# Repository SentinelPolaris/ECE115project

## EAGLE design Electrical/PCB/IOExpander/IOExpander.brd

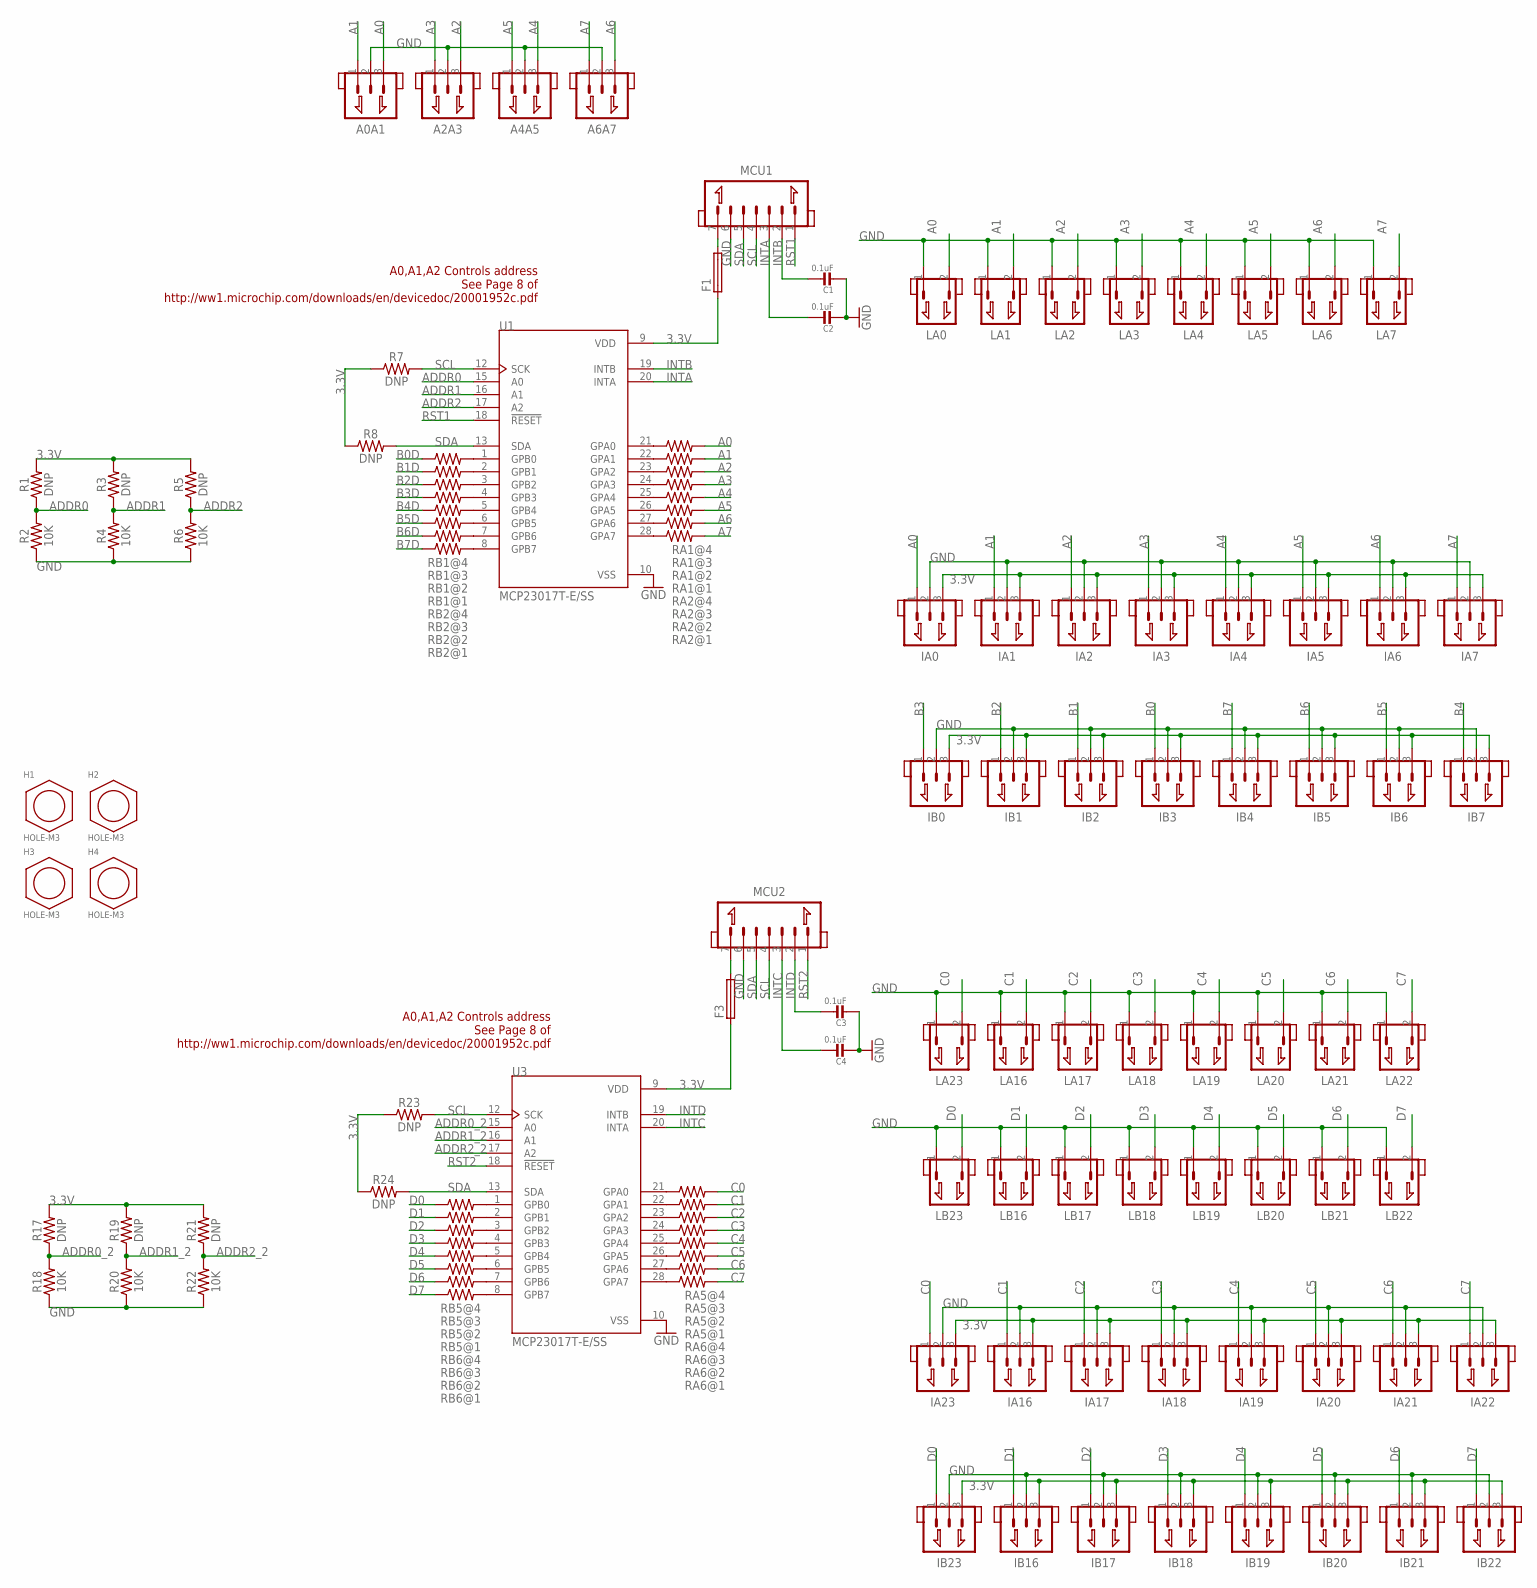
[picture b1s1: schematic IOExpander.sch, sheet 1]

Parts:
A0A1, A2A3, A4A5, A6A7: JST_1.25_3P; JST1.25_3P
C1, C2, C3, C4: 0.1uF; 0603
F1, F3: FUSE-0603; 0603
H1, H2, H3, H4: HOLE-M3; M3
IA0, IA1, IA2, IA3, IA4, IA5, IA6, IA7, IA16, IA17, IA18, IA19, IA20, IA21, IA22, IA23: JST_1.25_3P; JST1.25_3P
IB0, IB1, IB2, IB3, IB4, IB5, IB6, IB7, IB16, IB17, IB18, IB19, IB20, IB21, IB22, IB23: JST_1.25_3P; JST1.25_3P
LA0, LA1, LA2, LA3, LA4, LA5, LA6, LA7, LA16, LA17, LA18, LA19, LA20, LA21, LA22, LA23: JST_1.25_2P; JST1.25_2P
LB16, LB17, LB18, LB19, LB20, LB21, LB22, LB23: JST_1.25_2P; JST1.25_2P
MCU1, MCU2: JST_1.25_7P; JST1.25_7P
R1, R3, R5, R7, R8, R17, R19, R21, R23, R24: DNP; 0603
R2, R4, R6, R18, R20, R22: 10K; 0603
RA1, RA2, RA5, RA6: RESISTOR_ARRAY_1206_SEPARATE; RESCAF80P320X160X60-8N
RB1, RB2, RB5, RB6: RESISTOR_ARRAY_1206_SEPARATE_REVERSE; RESCAF80P320X160X60-8N
U1, U3: MCP23017T-E/SS; SOP65P780X200-28N

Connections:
3.3V: F1.1, F3.1, IA0.3, IA1.3, IA2.3, IA3.3, IA4.3, IA5.3, IA6.3, IA7.3, IA16.3, IA17.3, IA18.3, IA19.3, IA20.3, IA21.3, IA22.3, IA23.3, IB0.3, IB1.3, IB2.3, IB3.3, IB4.3, IB5.3, IB6.3, IB7.3, IB16.3, IB17.3, IB18.3, IB19.3, IB20.3, IB21.3, IB22.3, IB23.3, R1.2, R3.2, R5.2, R7.1, R8.1, R17.2, R19.2, R21.2, R23.1, R24.1, U1.9 (VDD), U3.9 (VDD); also elsewhere on the board
A0: A0A1.3, IA0.1, LA0.2, RA1.5 (2)
A1: A0A1.1, IA1.1, LA1.2, RA1.6 (2)
A2: A2A3.3, IA2.1, LA2.2, RA1.7 (2)
A3: A2A3.1, IA3.1, LA3.2, RA1.8 (2)
A4: A4A5.3, IA4.1, LA4.2, RA2.5 (2)
A5: A4A5.1, IA5.1, LA5.2, RA2.6 (2)
A6: A6A7.3, IA6.1, LA6.2, RA2.7 (2)
A7: A6A7.1, IA7.1, LA7.2, RA2.8 (2)
ADDR0: R1.1, R2.2, U1.15 (A0)
ADDR0_2: R17.1, R18.2, U3.15 (A0)
ADDR1: R3.1, R4.2, U1.16 (A1)
ADDR1_2: R19.1, R20.2, U3.16 (A1)
ADDR2: R5.1, R6.2, U1.17 (A2)
ADDR2_2: R21.1, R22.2, U3.17 (A2)
B0: IB3.1; also elsewhere on the board
B0D: RB1.5 (1); also elsewhere on the board
B1: IB2.1; also elsewhere on the board
B1D: RB1.6 (1); also elsewhere on the board
B2: IB1.1; also elsewhere on the board
B2D: RB1.7 (1); also elsewhere on the board
B3: IB0.1; also elsewhere on the board
B3D: RB1.8 (1); also elsewhere on the board
B4: IB7.1; also elsewhere on the board
B4D: RB2.5 (1); also elsewhere on the board
B5: IB6.1; also elsewhere on the board
B5D: RB2.6 (1); also elsewhere on the board
B6: IB5.1; also elsewhere on the board
B6D: RB2.7 (1); also elsewhere on the board
B7: IB4.1; also elsewhere on the board
B7D: RB2.8 (1); also elsewhere on the board
C0: IA23.1, LA23.2, RA5.5 (2)
C1: IA16.1, LA16.2, RA5.6 (2)
C2: IA17.1, LA17.2, RA5.7 (2)
C3: IA18.1, LA18.2, RA5.8 (2)
C4: IA19.1, LA19.2, RA6.5 (2)
C5: IA20.1, LA20.2, RA6.6 (2)
C6: IA21.1, LA21.2, RA6.7 (2)
C7: IA22.1, LA22.2, RA6.8 (2)
D0: IB23.1, LB23.2, RB5.5 (1)
D1: IB16.1, LB16.2, RB5.6 (1)
D2: IB17.1, LB17.2, RB5.7 (1)
D3: IB18.1, LB18.2, RB5.8 (1)
D4: IB19.1, LB19.2, RB6.5 (1)
D5: IB20.1, LB20.2, RB6.6 (1)
D6: IB21.1, LB21.2, RB6.7 (1)
D7: IB22.1, LB22.2, RB6.8 (1)
GND: A0A1.2, A2A3.2, A4A5.2, A6A7.2, C1.2, C2.2, C3.2, C4.2, IA0.2, IA1.2, IA2.2, IA3.2, IA4.2, IA5.2, IA6.2, IA7.2, IA16.2, IA17.2, IA18.2, IA19.2, IA20.2, IA21.2, IA22.2, IA23.2, IB0.2, IB1.2, IB2.2, IB3.2, IB4.2, IB5.2, IB6.2, IB7.2, IB16.2, IB17.2, IB18.2, IB19.2, IB20.2, IB21.2, IB22.2, IB23.2, LA0.1, LA1.1, LA2.1, LA3.1, LA4.1, LA5.1, LA6.1, LA7.1, LA16.1, LA17.1, LA18.1, LA19.1, LA20.1, LA21.1, LA22.1, LA23.1, LB16.1, LB17.1, LB18.1, LB19.1, LB20.1, LB21.1, LB22.1, LB23.1, MCU1.6, MCU2.6, R2.1, R4.1, R6.1, R18.1, R20.1, R22.1, U1.10 (VSS), U3.10 (VSS); also elsewhere on the board
INTA: C2.1, MCU1.3, U1.20 (INTA)
INTB: C1.1, MCU1.2, U1.19 (INTB)
INTC: C4.1, MCU2.3, U3.20 (INTA)
INTD: C3.1, MCU2.2, U3.19 (INTB)
unnamed: RA1.1, U1.24 (GPA3)
unnamed: RA1.2 (1), U1.23 (GPA2)
unnamed: RA1.3 (1), U1.22 (GPA1)
unnamed: RA1.4 (1), U1.21 (GPA0)
unnamed: RA2.1, U1.28 (GPA7)
unnamed: RA2.2 (1), U1.27 (GPA6)
unnamed: RA2.3 (1), U1.26 (GPA5)
unnamed: RA2.4 (1), U1.25 (GPA4)
unnamed: F1.2, MCU1.7
unnamed: RB1.1 (2), U1.4 (GPB3)
unnamed: RB1.2, U1.3 (GPB2)
unnamed: RB1.3 (2), U1.2 (GPB1)
unnamed: RB1.4 (2), U1.1 (GPB0)
unnamed: RB2.1 (2), U1.8 (GPB7)
unnamed: RB2.2, U1.7 (GPB6)
unnamed: RB2.3 (2), U1.6 (GPB5)
unnamed: RB2.4 (2), U1.5 (GPB4)
unnamed: F3.2, MCU2.7
unnamed: RB5.1 (2), U3.4 (GPB3)
unnamed: RB5.2, U3.3 (GPB2)
unnamed: RB5.3 (2), U3.2 (GPB1)
unnamed: RB5.4 (2), U3.1 (GPB0)
unnamed: RB6.1 (2), U3.8 (GPB7)
unnamed: RB6.2, U3.7 (GPB6)
unnamed: RB6.3 (2), U3.6 (GPB5)
unnamed: RB6.4 (2), U3.5 (GPB4)
unnamed: RA5.1, U3.24 (GPA3)
unnamed: RA5.2 (1), U3.23 (GPA2)
unnamed: RA5.3 (1), U3.22 (GPA1)
unnamed: RA5.4 (1), U3.21 (GPA0)
unnamed: RA6.1, U3.28 (GPA7)
unnamed: RA6.2 (1), U3.27 (GPA6)
unnamed: RA6.3 (1), U3.26 (GPA5)
unnamed: RA6.4 (1), U3.25 (GPA4)
RST1: MCU1.1, U1.18 (!RESET)
RST2: MCU2.1, U3.18 (!RESET)
SCL: MCU1.4, MCU2.4, R7.2, R23.2, U1.12 (SCK), U3.12 (SCK)
SDA: MCU1.5, MCU2.5, R8.2, R24.2, U1.13 (SDA), U3.13 (SDA)

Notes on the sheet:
A0,A1,A2 Controls address See Page 8 of http://ww1.microchip.com/downloads/en/devicedoc/20001952c.pdf

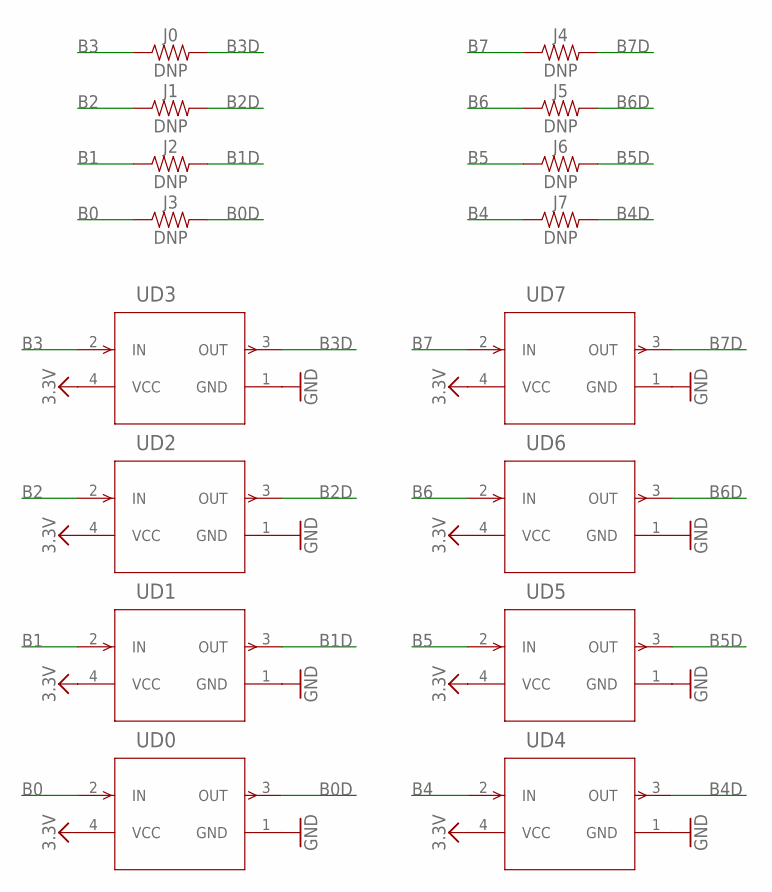
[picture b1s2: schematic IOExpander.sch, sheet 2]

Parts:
J0, J1, J2, J3, J4, J5, J6, J7: DNP; 0603
UD0, UD1, UD2, UD3, UD4, UD5, UD6, UD7: DEBOUNCE_MAX6816EUS+T; 21-0052F

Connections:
3.3V: UD0.4 (VCC), UD1.4 (VCC), UD2.4 (VCC), UD3.4 (VCC), UD4.4 (VCC), UD5.4 (VCC), UD6.4 (VCC), UD7.4 (VCC); also elsewhere on the board
B0: J3.1, UD0.2 (IN); also elsewhere on the board
B0D: J3.2, UD0.3 (OUT); also elsewhere on the board
B1: J2.1, UD1.2 (IN); also elsewhere on the board
B1D: J2.2, UD1.3 (OUT); also elsewhere on the board
B2: J1.1, UD2.2 (IN); also elsewhere on the board
B2D: J1.2, UD2.3 (OUT); also elsewhere on the board
B3: J0.1, UD3.2 (IN); also elsewhere on the board
B3D: J0.2, UD3.3 (OUT); also elsewhere on the board
B4: J7.1, UD4.2 (IN); also elsewhere on the board
B4D: J7.2, UD4.3 (OUT); also elsewhere on the board
B5: J6.1, UD5.2 (IN); also elsewhere on the board
B5D: J6.2, UD5.3 (OUT); also elsewhere on the board
B6: J5.1, UD6.2 (IN); also elsewhere on the board
B6D: J5.2, UD6.3 (OUT); also elsewhere on the board
B7: J4.1, UD7.2 (IN); also elsewhere on the board
B7D: J4.2, UD7.3 (OUT); also elsewhere on the board
GND: UD0.1 (GND), UD1.1 (GND), UD2.1 (GND), UD3.1 (GND), UD4.1 (GND), UD5.1 (GND), UD6.1 (GND), UD7.1 (GND); also elsewhere on the board

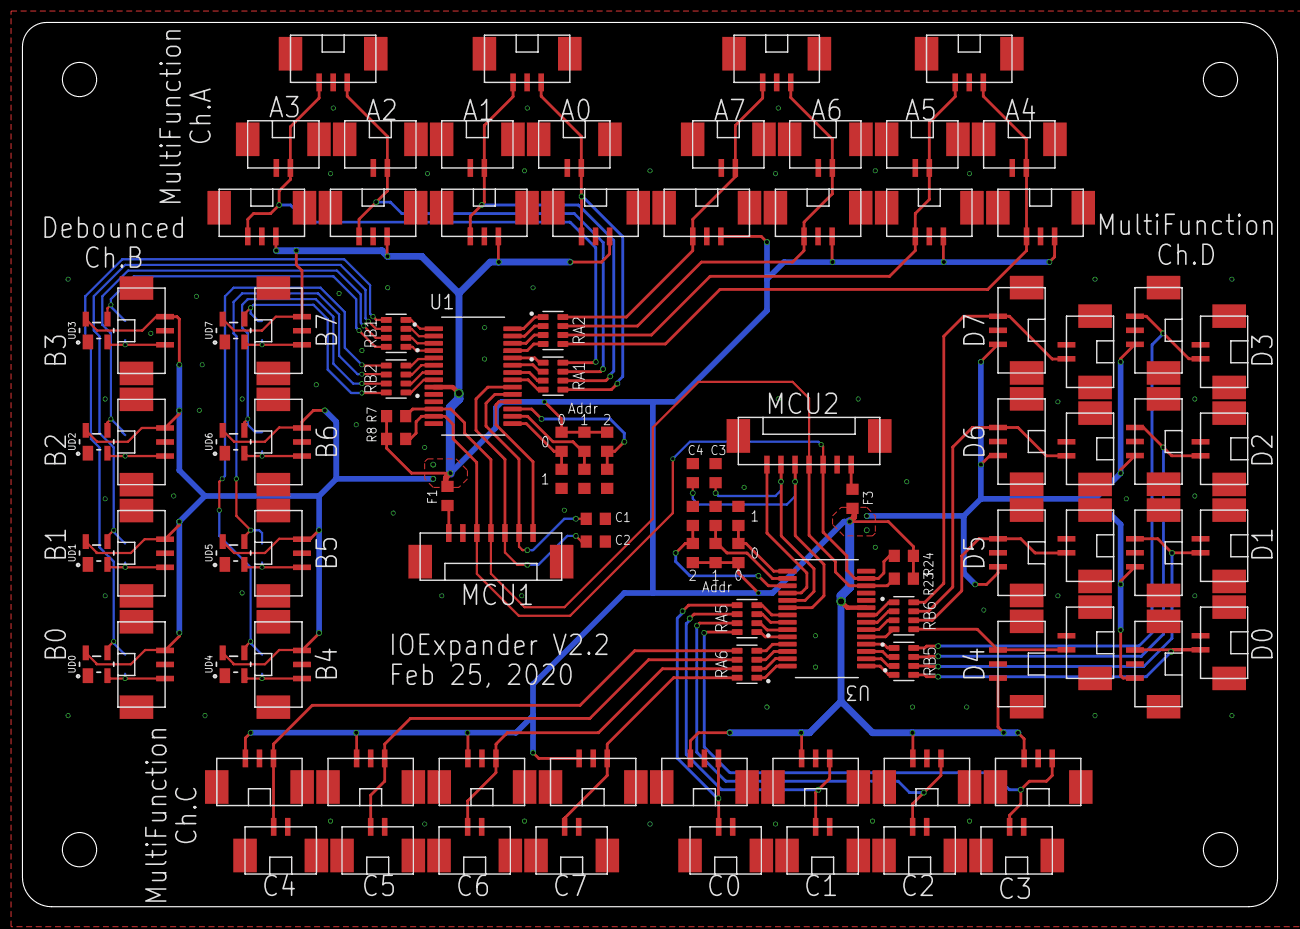
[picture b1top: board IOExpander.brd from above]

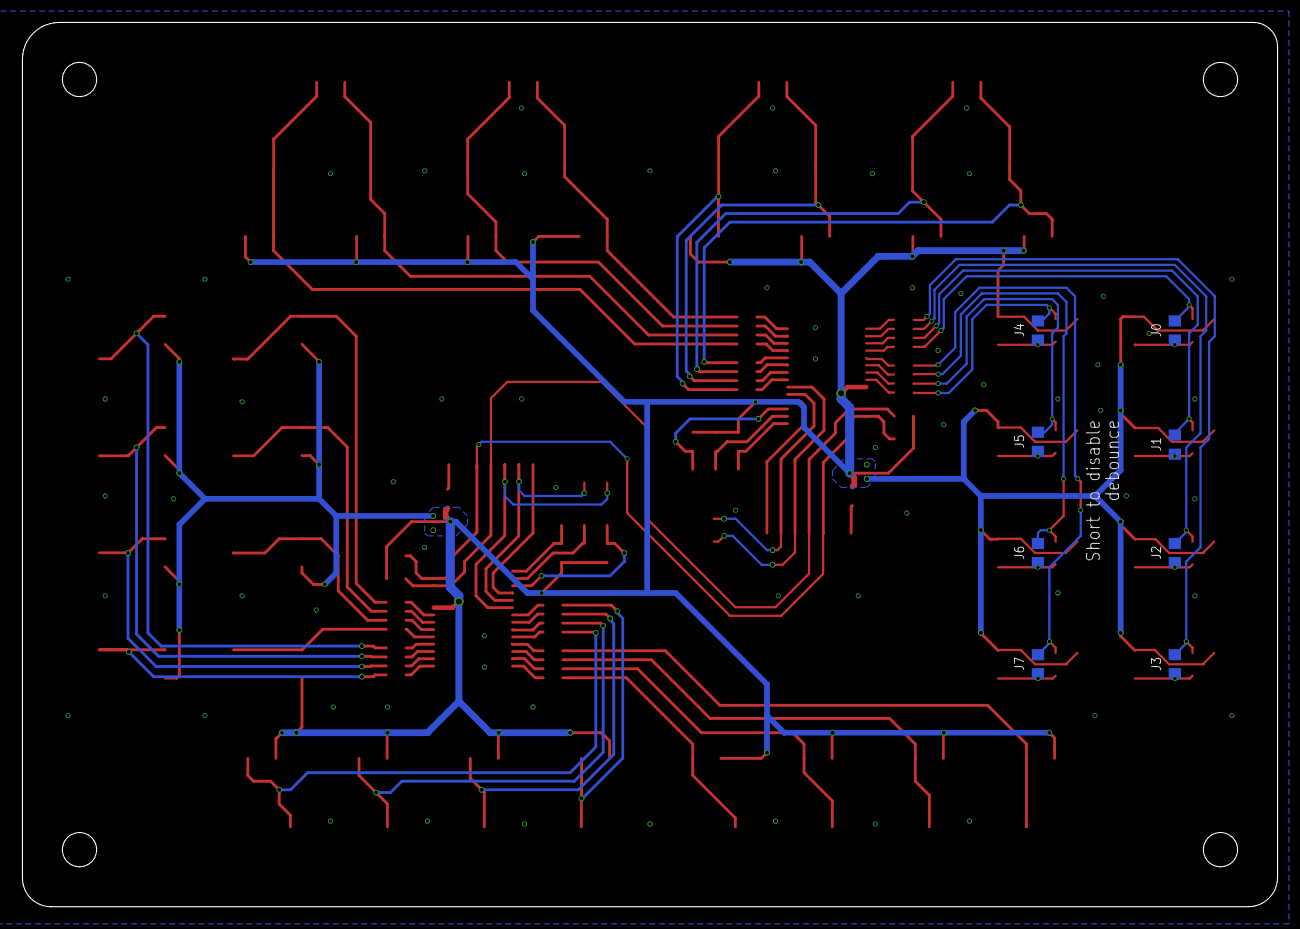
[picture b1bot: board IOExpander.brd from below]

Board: 2 copper layers, 111.8 x 78.7 mm, 114 parts (8 on the bottom side), 90 nets.

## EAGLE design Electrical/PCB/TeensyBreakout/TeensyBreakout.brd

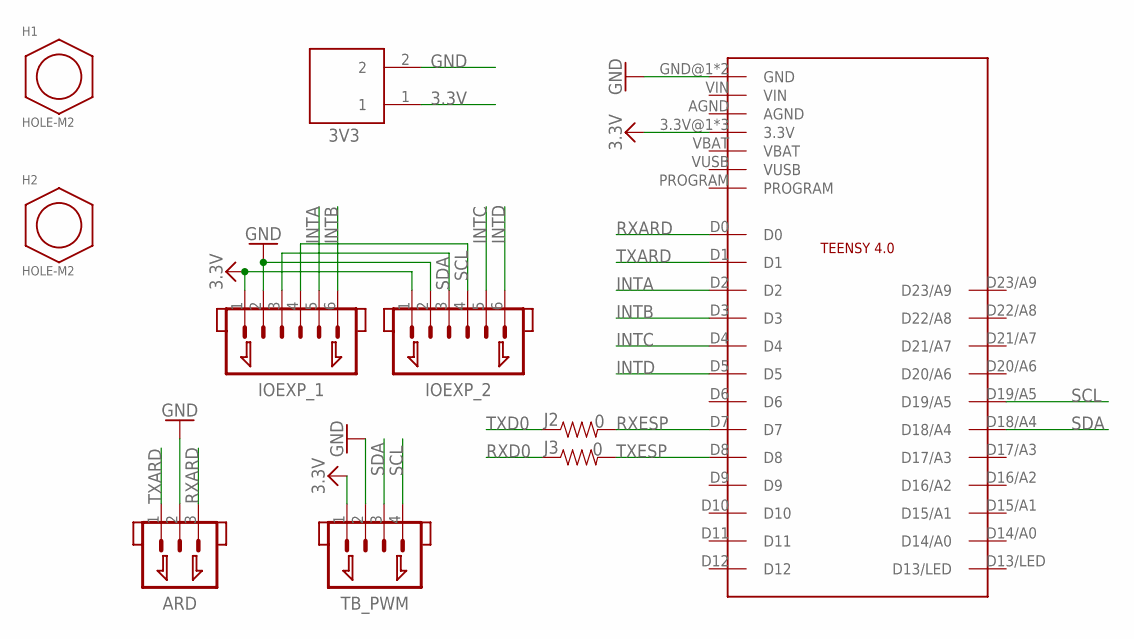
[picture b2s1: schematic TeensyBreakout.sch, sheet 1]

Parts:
3V3: TERMINAL; ED555/2DS
ARD: JST_1.25_3P; JST1.25_3P
H1, H2: HOLE-M2; M2
IOEXP_1, IOEXP_2: JST_1.25_6P; JST1.25_6P
J2, J3: 0; 0603
TB_PWM: JST_1.25_4P; JST1.25_4P
U$1: TEENSY4.0

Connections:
3.3V: 3V3.1, IOEXP_1.1, IOEXP_2.1, TB_PWM.1, U$1.3.3V@1 (3.3V), U$1.3.3V@2 (3.3V), U$1.ON/OFF (3.3V); also elsewhere on the board
GND: 3V3.2, ARD.2, IOEXP_1.2, IOEXP_2.2, TB_PWM.2, U$1.GND@1 (GND), U$1.GND@2 (GND); also elsewhere on the board
INTA: IOEXP_1.5, U$1.D2
INTB: IOEXP_1.6, U$1.D3
INTC: IOEXP_2.5, U$1.D4
INTD: IOEXP_2.6, U$1.D5
RST1: IOEXP_1.7, U$1.D9
RST2: IOEXP_2.7, U$1.D10
RXARD: ARD.3, U$1.D0
RXD0: J3.1; also elsewhere on the board
RXESP: J2.2, U$1.D7
SCL: IOEXP_1.4, IOEXP_2.4, TB_PWM.4, U$1.D19/A5
SDA: IOEXP_1.3, IOEXP_2.3, TB_PWM.3, U$1.D18/A4
TXARD: ARD.1, U$1.D1
TXD0: J2.1; also elsewhere on the board
TXESP: J3.2, U$1.D8

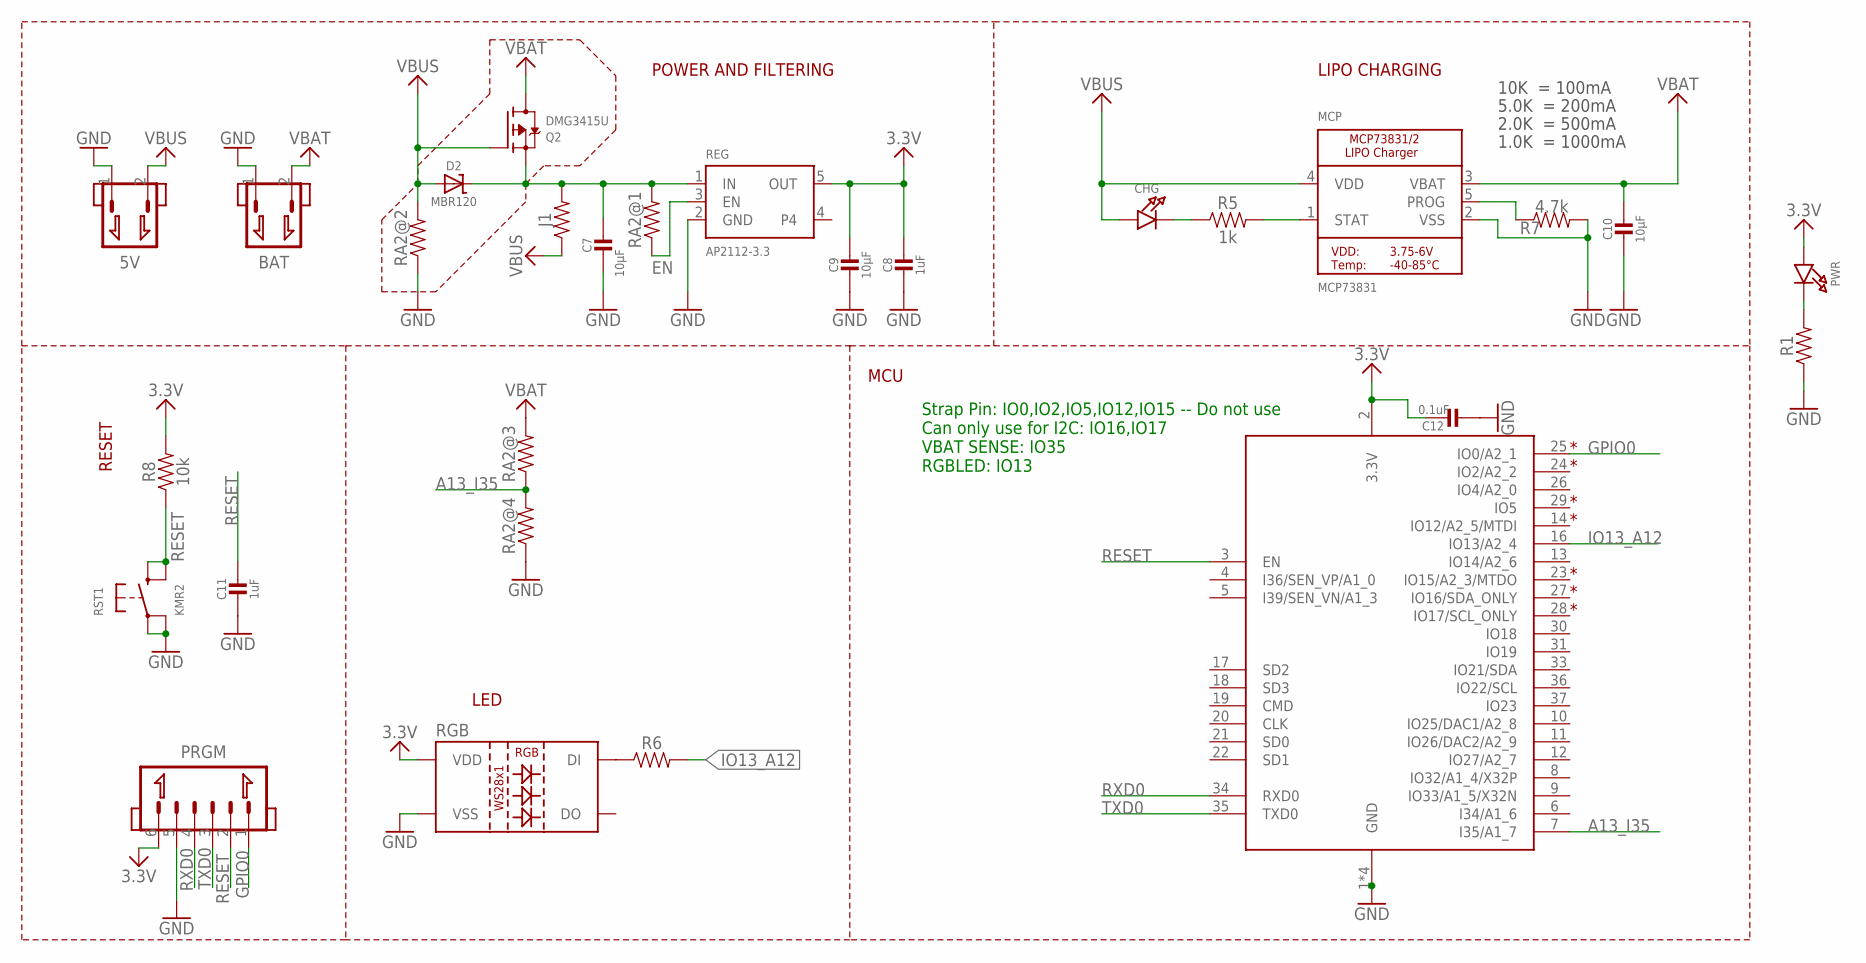
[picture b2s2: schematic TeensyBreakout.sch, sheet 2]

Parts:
5V: JST_PH_2.0_2P
BAT: JSTPH; JST_PH_2.0_2P
C7, C10: 10µF; 0805
C8, C11: 1uF; 0603
C9: 10µF; 0603
C12: 0.1uF; 0603
CHG: LED0603; CHIPLED_0603
D2: MBR120; SOD-123
J1: 0603
MCP: MCP73831; MICROBUILDER_SOT23-5
PRGM: JST_1.25_6P; JST1.25_6P
PWR: LED0603; CHIPLED_0603
Q2: DMG3415U; SOT23-WIDE
R1, R6: 0603
R5: 1k; 0603
R7: 4.7k; 0603
R8: 10k; 0603
RA2: RESISTOR_ARRAY_1206_SEPARATE_REVERSE; RESCAF80P320X160X60-8N
REG: AP2112-3.3; MICROBUILDER_SOT23-5
RGB: LED_WS2812; LED-TRICOLOR-5050-IC
RST1: KMR2; BTN_KMR2_4.6X2.8
X1: ESP32_WROOM32; WROOM32

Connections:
3.3V: C8.1, C9.1, C12.1, PRGM.6, PWR.A, R8.2, REG.5 (OUT), RGB.VDD, X1.2 (3.3V); also elsewhere on the board
A13_I35: RA2.4 (2), RA2.6 (1), X1.7 (I35/A1_7)
EN: RA2.8 (1), REG.3 (EN)
GND: 5V.1, BAT.1, C7.2, C8.2, C9.2, C10.2, C11.2, C12.2, MCP.2 (VSS), PRGM.5, R1.1, R7.2, RA2.5 (1), RA2.7 (1), REG.2 (GND), RGB.VSS, RST1.A, RST1.A' (P1), X1.1 (GND), X1.15 (GND), X1.38 (GND), X1.P$1 (GND); also elsewhere on the board
GPIO0: PRGM.1, X1.25 (IO0/A2_1)
IO13_A12: R6.2, X1.16 (IO13/A2_4)
unnamed: PWR.C, R1.2
unnamed: CHG.C, R5.1
unnamed: MCP.1 (STAT), R5.2
unnamed: MCP.5 (PROG), R7.1
unnamed: C7.1, D2.C, J1.2, Q2.2 (S), RA2.1 (2), REG.1 (IN)
unnamed: R6.1, RGB.DIN (DI)
RESET: C11.1, PRGM.2, R8.1, RST1.B (S), RST1.B' (S1), X1.3 (EN)
RXD0: PRGM.4, X1.34 (RXD0); also elsewhere on the board
TXD0: PRGM.3, X1.35 (TXD0); also elsewhere on the board
VBAT: BAT.2, C10.1, MCP.3 (VBAT), Q2.3 (D), RA2.3 (2)
VBUS: 5V.2, CHG.A, D2.A, J1.1, MCP.4 (VDD), Q2.1 (G), RA2.2

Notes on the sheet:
POWER AND FILTERING
RESET
10K = 100mA
5.0K = 200mA
2.0K = 500mA
1.0K = 1000mA
LIPO CHARGING
LED
Strap Pin: IO0,IO2,IO5,IO12,IO15 -- Do not use Can only use for I2C: IO16,IO17 VBAT SENSE: IO35 RGBLED: IO13
MCU

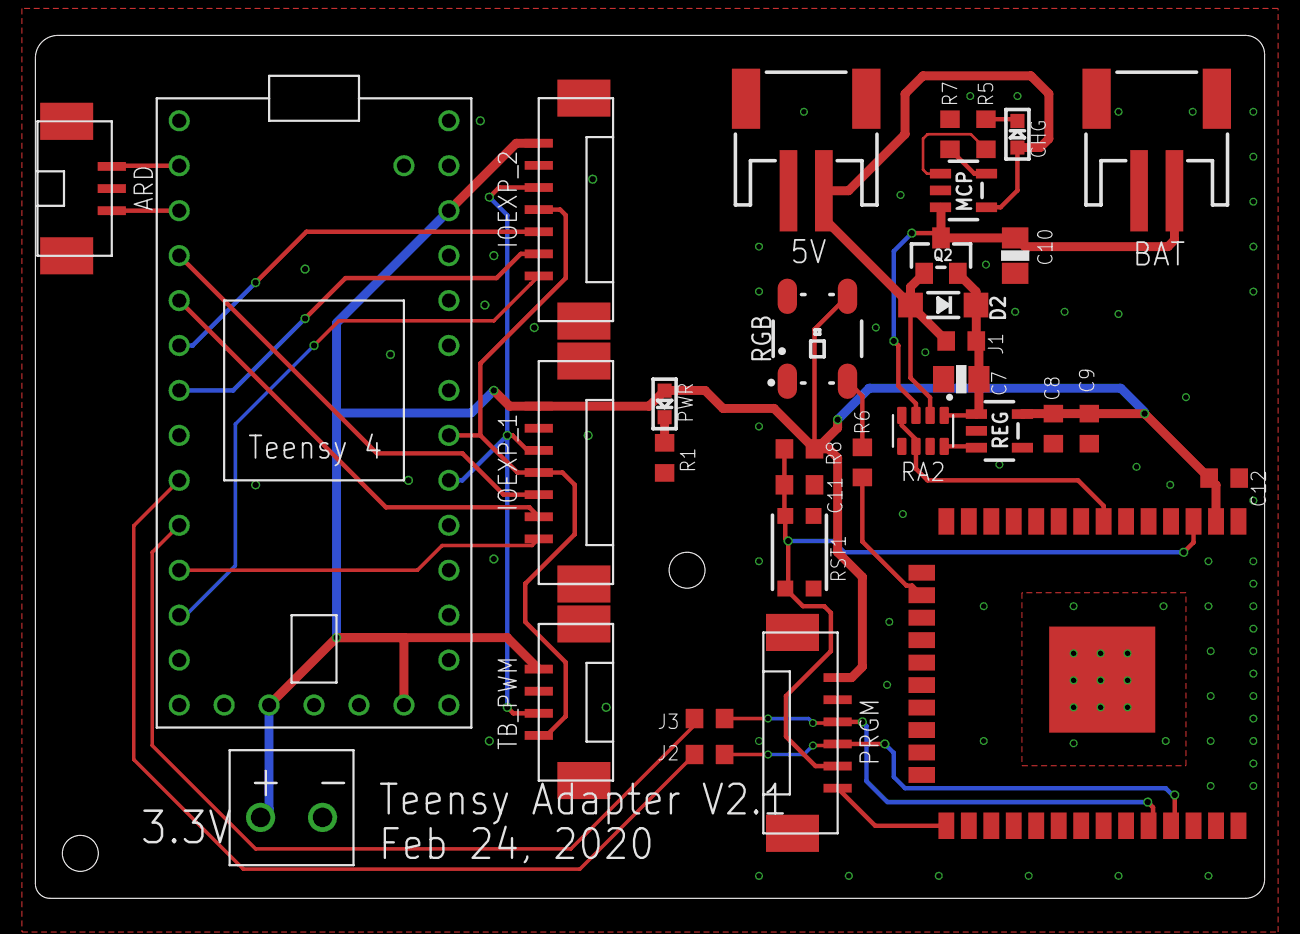
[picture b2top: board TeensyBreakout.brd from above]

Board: 2 copper layers, 69.5 x 48.8 mm, 35 parts (0 on the bottom side), 29 nets.

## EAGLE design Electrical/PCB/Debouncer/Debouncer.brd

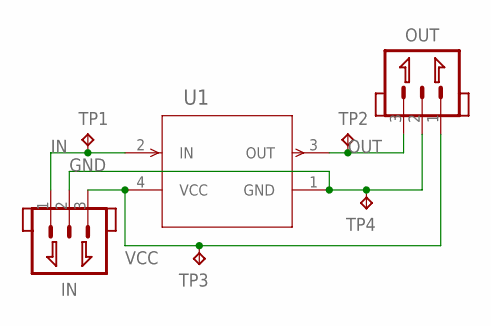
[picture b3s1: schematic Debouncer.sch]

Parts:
IN: JST_1.25_3P; JST1.25_3P
OUT: JST_1.25_3P; JST1.25_3P
TP1, TP2, TP3, TP4: TPPAD1-13; P1-13
U1: DEBOUNCE_MAX6816EUS+T; 21-0052F

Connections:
GND: IN.2, OUT.2, TP4.TP, U1.1 (GND)
IN: IN.1, TP1.TP, U1.2 (IN)
OUT: OUT.3, TP2.TP, U1.3 (OUT)
VCC: IN.3, OUT.1, TP3.TP, U1.4 (VCC)

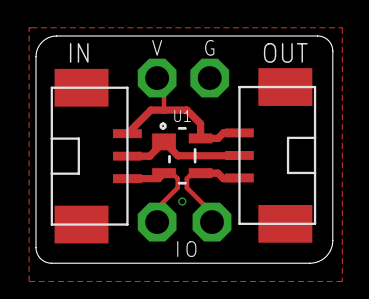
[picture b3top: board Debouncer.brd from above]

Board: 2 copper layers, 16.5 x 12.6 mm, 7 parts (0 on the bottom side), 4 nets.

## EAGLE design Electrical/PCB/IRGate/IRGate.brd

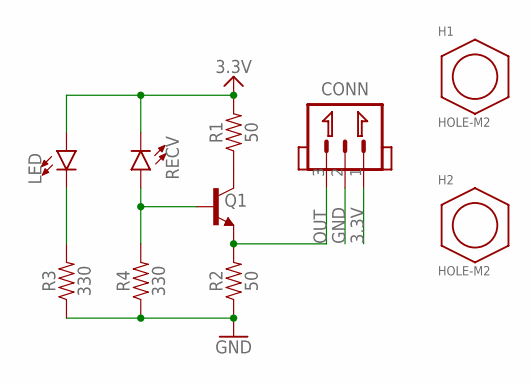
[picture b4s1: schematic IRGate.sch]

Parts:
CONN: JST_1.25_3P; JST1.25_3P
H1, H2: HOLE-M2; M2
LED: LED-IRTSAL6100; LED_5MM
Q1: NPNSOT23-3; SOT23-3
R1, R2: 50; 0603
R3, R4: 330; 0603
RECV: LED-IRSIDE_EMITTER; LTE-302

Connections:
3.3V: CONN.1, LED.A, R1.2, RECV.C
GND: CONN.2, R2.1, R3.1, R4.1
unnamed: Q1.3 (C), R1.1
unnamed: Q1.1 (B), R4.2, RECV.A
unnamed: LED.K (C), R3.2
OUT: CONN.3, Q1.2 (E), R2.2

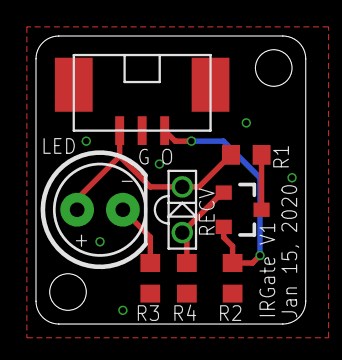
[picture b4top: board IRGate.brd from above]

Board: 2 copper layers, 15.0 x 16.0 mm, 10 parts (0 on the bottom side), 6 nets.

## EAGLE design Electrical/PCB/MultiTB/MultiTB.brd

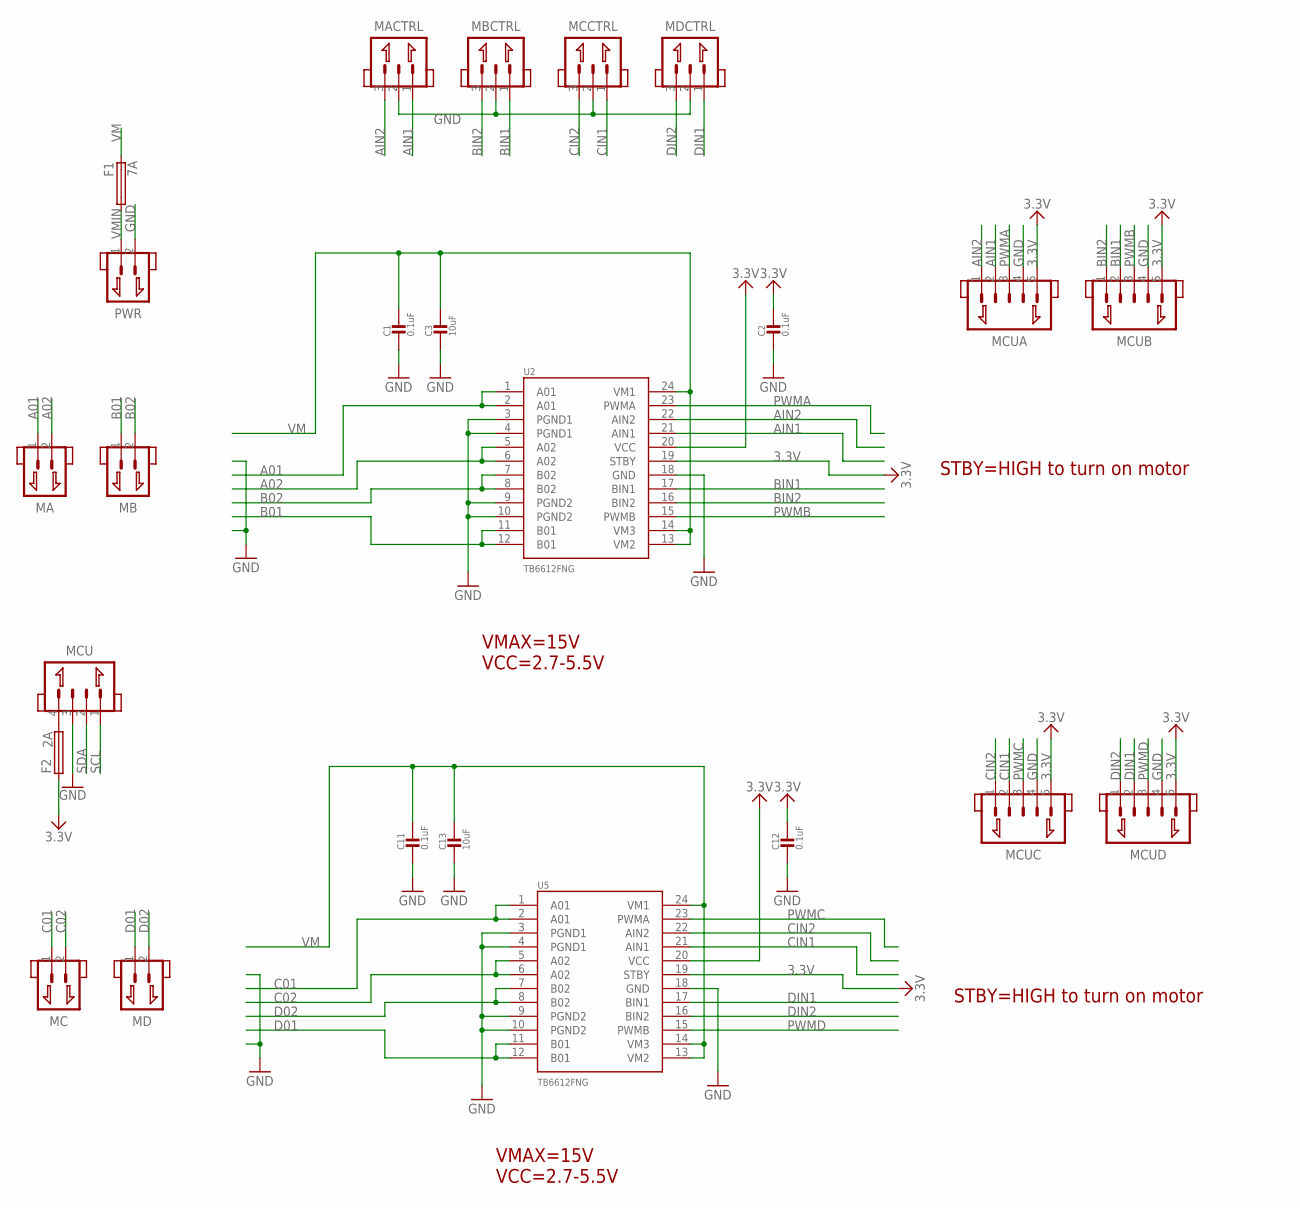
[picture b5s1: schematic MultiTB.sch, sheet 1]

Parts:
C1, C2, C11, C12: 0.1uF; 0603
C3, C13: 10uF; 0805
F1: 7A; 1206
F2: 2A; 0603
MA: JST_XH_2.54_2P
MACTRL: JST_1.25_3P; JST1.25_3P
MB: JST_XH_2.54_2P
MBCTRL: JST_1.25_3P; JST1.25_3P
MC: JST_XH_2.54_2P
MCCTRL: JST_1.25_3P; JST1.25_3P
MCU: JST_1.25_4P; JST1.25_4P
MCUA: JST_1.25_5P; JST1.25_5P
MCUB: JST_1.25_5P; JST1.25_5P
MCUC: JST_1.25_5P; JST1.25_5P
MCUD: JST_1.25_5P; JST1.25_5P
MD: JST_XH_2.54_2P
MDCTRL: JST_1.25_3P; JST1.25_3P
PWR: JST_XH_2.54_2P
U2, U5: TB6612FNG; SSOP24

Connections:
3.3V: C2.1, C12.1, F2.1, MCUA.5, MCUB.5, MCUC.5, MCUD.5, U2.19 (STBY), U2.20 (VCC), U5.19 (STBY), U5.20 (VCC); also elsewhere on the board
A01: MA.1, U2.1 (A01), U2.2 (A01)
A02: MA.2, U2.5 (A02), U2.6 (A02)
AIN1: MACTRL.1, MCUA.2, U2.21 (AIN1)
AIN2: MACTRL.3, MCUA.1, U2.22 (AIN2)
B01: MB.1, U2.11 (B01), U2.12 (B01)
B02: MB.2, U2.7 (B02), U2.8 (B02)
BIN1: MBCTRL.1, MCUB.2, U2.17 (BIN1)
BIN2: MBCTRL.3, MCUB.1, U2.16 (BIN2)
C01: MC.1, U5.1 (A01), U5.2 (A01)
C02: MC.2, U5.5 (A02), U5.6 (A02)
CIN1: MCCTRL.1, MCUC.2, U5.21 (AIN1)
CIN2: MCCTRL.3, MCUC.1, U5.22 (AIN2)
D01: MD.1, U5.11 (B01), U5.12 (B01)
D02: MD.2, U5.7 (B02), U5.8 (B02)
DIN1: MCUD.2, MDCTRL.1, U5.17 (BIN1)
DIN2: MCUD.1, MDCTRL.3, U5.16 (BIN2)
GND: C1.2, C2.2, C3.2, C11.2, C12.2, C13.2, MACTRL.2, MBCTRL.2, MCCTRL.2, MCU.3, MCUA.4, MCUB.4, MCUC.4, MCUD.4, MDCTRL.2, PWR.2, U2.3 (PGND1), U2.4 (PGND1), U2.9 (PGND2), U2.10 (PGND2), U2.18 (GND), U5.3 (PGND1), U5.4 (PGND1), U5.9 (PGND2), U5.10 (PGND2), U5.18 (GND); also elsewhere on the board
unnamed: F2.2, MCU.4
PWMA: MCUA.3, U2.23 (PWMA); also elsewhere on the board
PWMB: MCUB.3, U2.15 (PWMB); also elsewhere on the board
PWMC: MCUC.3, U5.23 (PWMA); also elsewhere on the board
PWMD: MCUD.3, U5.15 (PWMB); also elsewhere on the board
SCL: MCU.1; also elsewhere on the board
SDA: MCU.2; also elsewhere on the board
VM: C1.1, C3.1, C11.1, C13.1, F1.2, U2.13 (VM2), U2.14 (VM3), U2.24 (VM1), U5.13 (VM2), U5.14 (VM3), U5.24 (VM1)
VMIN: F1.1, PWR.1

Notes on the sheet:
VMAX=15V VCC=2.7-5.5V
STBY=HIGH to turn on motor

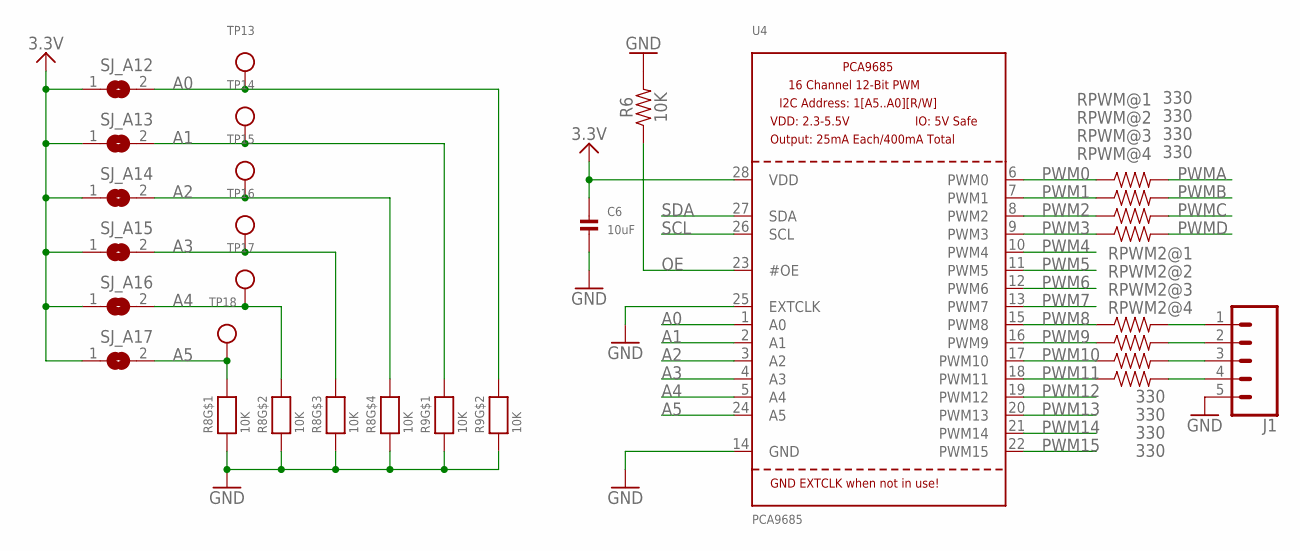
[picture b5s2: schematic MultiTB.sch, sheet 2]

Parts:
C6: 10uF; 0805
J1: CONN_05; 1X05
R6: 10K; 0603
R8, R9: 10K; RESPACK_4X0603
RPWM, RPWM2: 330; RESCAF80P320X160X60-8N
SJ_A12, SJ_A13, SJ_A14, SJ_A15, SJ_A16, SJ_A17: SOLDERJUMPERREFLOW_NOPASTE; SOLDERJUMPER_REFLOW_NOPASTE
TP13, TP14, TP15, TP16, TP17, TP18: TESTPOINTROUND2MM; TESTPOINT_ROUND_2MM
U4: PCA9685; TSSOP28

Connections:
3.3V: C6.1, SJ_A12.1, SJ_A13.1, SJ_A14.1, SJ_A15.1, SJ_A16.1, SJ_A17.1, U4.28 (VDD); also elsewhere on the board
A0: R9.7 (2), SJ_A12.2, TP13.P$1, U4.1 (A0)
A1: R9.8 (2), SJ_A13.2, TP14.P$1, U4.2 (A1)
A2: R8.5 (2), SJ_A14.2, TP15.P$1, U4.3 (A2)
A3: R8.6 (2), SJ_A15.2, TP16.P$1, U4.4 (A3)
A4: R8.7 (2), SJ_A16.2, TP17.P$1, U4.5 (A4)
A5: R8.8 (2), SJ_A17.2, TP18.P$1, U4.24 (A5)
GND: C6.2, J1.5, R6.2, R8.1, R8.2 (1), R8.3 (1), R8.4 (1), R9.1, R9.2 (1), U4.14 (GND), U4.25 (EXTCLK); also elsewhere on the board
unnamed: J1.1, RPWM2.1 (2)
unnamed: J1.2, RPWM2.2
unnamed: J1.3, RPWM2.3 (2)
unnamed: J1.4, RPWM2.4 (2)
OE: R6.1, U4.23 (#OE)
PWM0: RPWM.8 (1), U4.6 (PWM0)
PWM1: RPWM.7 (1), U4.7 (PWM1)
PWM2: RPWM.6 (1), U4.8 (PWM2)
PWM3: RPWM.5 (1), U4.9 (PWM3)
PWM4: U4.10 (PWM4)
PWM5: U4.11 (PWM5)
PWM6: U4.12 (PWM6)
PWM7: U4.13 (PWM7)
PWM8: RPWM2.8 (1), U4.15 (PWM8)
PWM9: RPWM2.7 (1), U4.16 (PWM9)
PWM10: RPWM2.6 (1), U4.17 (PWM10)
PWM11: RPWM2.5 (1), U4.18 (PWM11)
PWM12: U4.19 (PWM12)
PWM13: U4.20 (PWM13)
PWM14: U4.21 (PWM14)
PWM15: U4.22 (PWM15)
PWMA: RPWM.1 (2); also elsewhere on the board
PWMB: RPWM.2; also elsewhere on the board
PWMC: RPWM.3 (2); also elsewhere on the board
PWMD: RPWM.4 (2); also elsewhere on the board
SCL: U4.26 (SCL); also elsewhere on the board
SDA: U4.27 (SDA); also elsewhere on the board

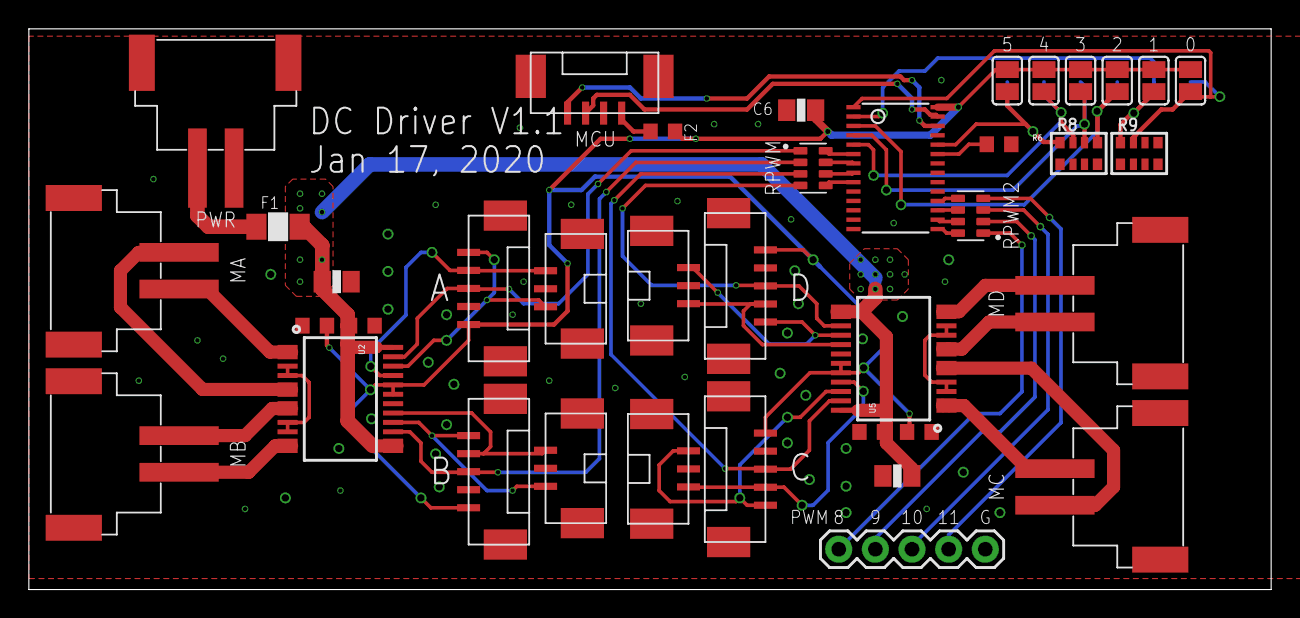
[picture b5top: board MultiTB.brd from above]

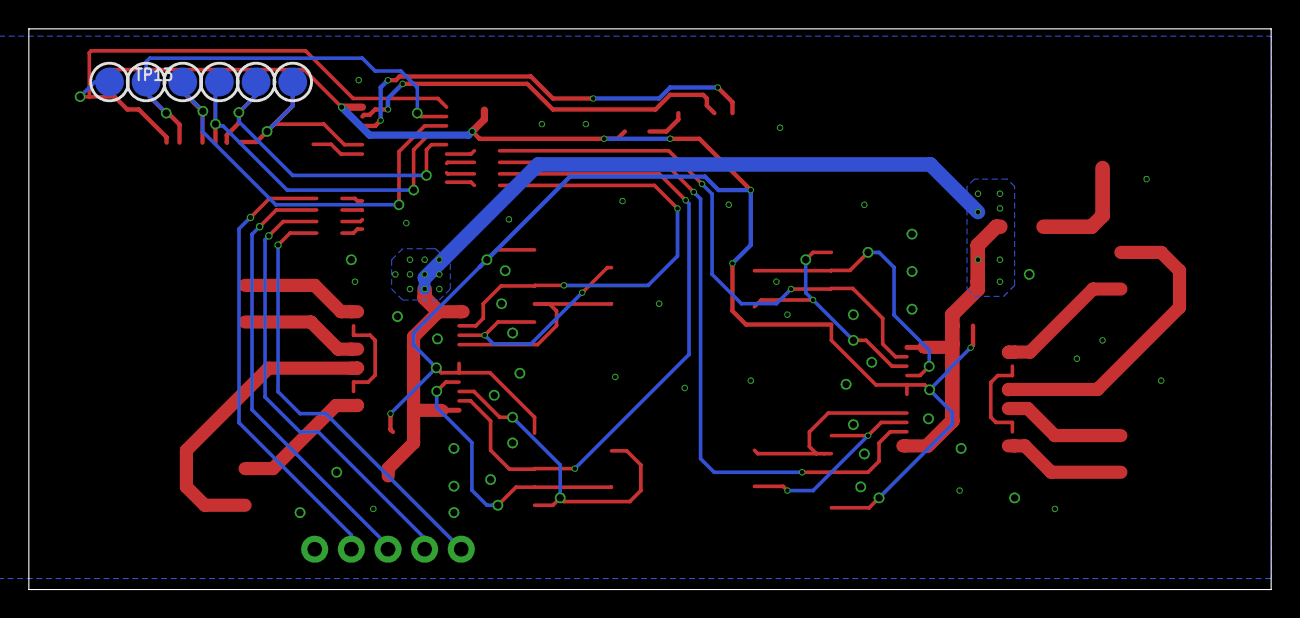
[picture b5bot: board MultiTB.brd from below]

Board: 2 copper layers, 86.1 x 38.9 mm, 44 parts (6 on the bottom side), 46 nets.

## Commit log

2020-01-15 add cad files
2020-01-15 cleanup
2020-01-15 PCBs V1 WIP
2020-01-17 PCB Batch #1
2020-01-22 added filpper design
2020-01-23 walls; final assembly init
2020-01-27 cad files cleanup; ramp
2020-01-28 bump 1/27
2020-01-28 bump eagle 1/27
2020-01-28 servo ATTiny85 code
2020-01-30 fix servo randomly stop (software servo)
2020-01-30 add servo cad
2020-01-30 tunnel walls, IR gate, flipper asm
2020-01-30 software bump 1.30
2020-01-31 bump cad 1/31
2020-01-31 Add EM guide
2020-01-31 cad ramp servo update
2020-02-01 ramp v1
2020-02-01 Add solenoid
2020-02-03 teensy init drivers etc
2020-02-03 bump cad 2/3
2020-02-04 pwm working; pwm test thread
2020-02-04 fix gitignore
2020-02-05 bump software 2/5; a lot of struggle in getting interrupt on ioexp to work :/
2020-02-06 io interrupt from mcp working; refactor
2020-02-07 bump cad 2/7
2020-02-10 soldnoid/ramp guides
2020-02-14 added launcher coil
2020-02-14 ramp update; em launcher
2020-02-14 cad bump 2/14
2020-02-14 bump cad 2/14
2020-02-16 bump cad 2/15
2020-02-17 holes
2020-02-18 init RGB Panel software
2020-02-18 add rgb panel
2020-02-18 more holes
2020-02-18 arch update
2020-02-21 add flipper holder
2020-02-24 teensyBreakout V2, debouncer
2020-02-24 bump pcb 2/24
2020-02-25 io expander fix V2.2 -- add 0.1uF to GND on IRQ pin
2020-02-25 update working io expander interrupt code
2020-02-27 bump 2/26
2020-02-27 freertos init
2020-02-27 update gitignore
2020-02-27 arch update; freertos queue testing
2020-02-27 cpu usage not yet working
2020-02-28 all task framework done
2020-02-28 cpu usage fix: updated freertos according to https://github.com/discord-intech/FreeRTOS-Teensy4/issues/3
2020-02-28 os refactor; fixing audio wip (put audioplayer onto a separate teensy)
2020-03-01 audio working; solenoid working
2020-03-04 bump software 3/3: basically working
2020-03-04 add playfield back support
2020-03-06 Ramp V3
2020-03-10 small addition
2020-03-10 fix solenoid bouncing 3/10
2020-03-11 working interrupt software 3/10
2020-03-11 io exp2 working
2020-03-11 audio mixer working; ioexp2 working
2020-03-12 fix motor
2020-03-12 close to final

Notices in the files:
parts and their libraries:
SparkFun-LED: Licensing: Creative Commons ShareAlike 4.0 International - https://creativecommons.org/licenses/by-sa/4.0
